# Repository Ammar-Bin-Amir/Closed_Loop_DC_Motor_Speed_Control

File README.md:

# Closed Loop DC Motor Speed Control

A speed control system's goal is to keep the motor's speed constant under a variety of circumstances. The DC motor is a nonlinear device in practice and speed variations are caused by disturbances, changes in load demand, etc. In this projet, the PID controller algorithm, a common controller in industries, has been implemented which overcome the disturbances occurring in the system and establishes the motor speed to the desired value without any human assistance.

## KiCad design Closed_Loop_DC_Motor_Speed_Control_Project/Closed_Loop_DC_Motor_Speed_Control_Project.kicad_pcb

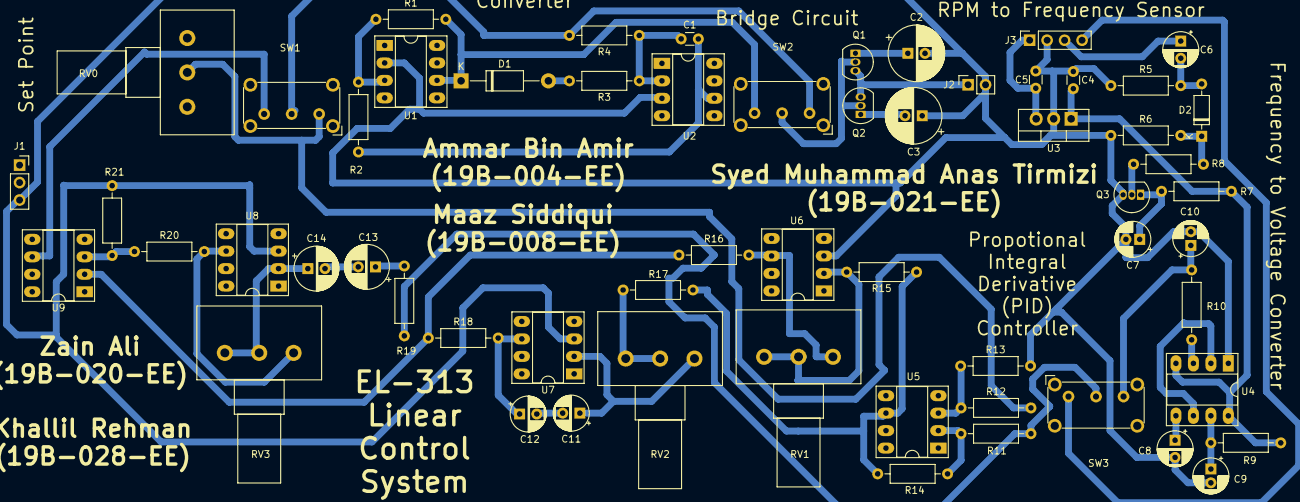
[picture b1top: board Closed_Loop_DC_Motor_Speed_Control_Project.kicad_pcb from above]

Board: 2 copper layers, 59 parts (0 on the bottom side), 41 nets.

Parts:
C1: 0.01μF; C_Disc_D3.0mm_W1.6mm_P2.50mm
C2, C3: 470μF,16VDC; CP_Radial_D8.0mm_P2.50mm
C4: 0.22μF; C_Disc_D3.0mm_W1.6mm_P2.50mm
C5: 0.1μF; C_Disc_D3.0mm_W1.6mm_P2.50mm
C6: 47μF; CP_Radial_D5.0mm_P2.50mm
C7, C9, C10: 0.022μF; CP_Radial_D5.0mm_P2.00mm
C8: 0.1μF; CP_Radial_D5.0mm_P2.50mm
C11, C12: 470μF; CP_Radial_D5.0mm_P2.50mm
C13, C14: 100μF; CP_Radial_D6.3mm_P2.50mm
D1: 1N4001; D_DO-41_SOD81_P12.70mm_Horizontal
D2: 1N4149; D_DO-35_SOD27_P7.62mm_Horizontal
J1: Power Supply; PinSocket_1x03_P2.54mm_Vertical
J2: DC Motor; PinSocket_1x02_P2.54mm_Vertical
J3: IR Sensor; PinSocket_1x04_P2.54mm_Vertical
Q1: BC547; TO-92_Inline
Q2: BC557; TO-92_Inline
Q3: BC337; TO-92_Inline
R1, R2, R3, R4, R11, R12, R13, R14, R15, R16, R18, R20, R21: 10kΩ; R_Axial_DIN0207_L6.3mm_D2.5mm_P10.16mm_Horizontal
R5, R17: 1kΩ; R_Axial_DIN0207_L6.3mm_D2.5mm_P10.16mm_Horizontal
R6, R7, R9: 47kΩ; R_Axial_DIN0207_L6.3mm_D2.5mm_P10.16mm_Horizontal
R8: 15kΩ; R_Axial_DIN0207_L6.3mm_D2.5mm_P10.16mm_Horizontal
R10: 4.7kΩ; R_Axial_DIN0207_L6.3mm_D2.5mm_P10.16mm_Horizontal
R19: 200Ω; R_Axial_DIN0207_L6.3mm_D2.5mm_P10.16mm_Horizontal
RV0, RV1, RV2, RV3: 100kΩ; Potentiometer_Alps_RK163_Single_Horizontal
SW1, SW2, SW3: SW_DPDT_x2; SW_E-Switch_EG1224_SPDT_Angled
U1, U2, U5, U6, U7, U8, U9: LM741; DIP-8_W7.62mm_Socket_LongPads
U3: LM7805_TO220; TO-220-3_Vertical
U4: LM555xM; DIP-8_W7.62mm_Socket_LongPads

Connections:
+12V: C2.1, C4.1, J1.1, Q1.1, R8.2, R9.2, RV0.1, U1.7, U2.7, U3.1, U4.4, U4.8, U5.7, U6.7, U7.7, U8.7, U9.7
-12V: C3.2, J1.2, Q2.1, RV0.3, U1.4, U2.4, U5.4, U6.4, U7.4, U8.4, U9.4
A_out: J3.4, SW3.1
BridgeIn: Q1.2, Q2.2, SW2.2
BridgeOut: J2.1, Q1.3, Q2.3
D_out: C6.1, J3.3
Derivative: R20.2, RV3.3, U8.6
F_to_V: C10.1, R10.1, SW3.3
GND: C2.2, C3.1, C4.2, C5.2, C7.2, C8.2, C9.2, C10.2, J1.3, J2.2, J3.2, Q3.3, R5.1, R6.1, R13.2, R21.2, U1.2, U2.3, U3.2, U4.1, U6.3, U7.3, U8.3
Input: R4.2, SW1.2, SW2.1
Integral: C12.1, R18.2, U7.6
unnamed: C1.1, R3.1, R4.1, U2.2
unnamed: C1.2, R2.1, U2.6
unnamed: C5.1, J3.1, U3.3
unnamed: C6.2, D2.2, R5.2
unnamed: C7.1, Q3.1, R8.1
unnamed: C8.1, U4.5
unnamed: C9.1, R9.1, U4.7
unnamed: C11.1, RV2.3, U7.2
unnamed: C11.2, C12.2
unnamed: C13.1, R19.1
unnamed: C13.2, C14.2
unnamed: C14.1, RV3.1, RV3.2, U8.2
unnamed: D1.2, R3.2
unnamed: D2.1, R6.2, R7.1
unnamed: Q3.2, R7.2
unnamed: R1.1, R2.2, U1.3
unnamed: R10.2, U4.3
unnamed: R11.1, R14.2, U5.2
unnamed: R12.1, R13.1, U5.3
unnamed: R14.1, R15.1, R17.1, U5.6
unnamed: R15.2, RV1.1, RV1.2, U6.2
unnamed: R16.1, R18.1, U9.2
unnamed: R17.2, RV2.1, RV2.2
unnamed: R20.1, R21.1, U9.3
unnamed: U4.2, U4.6
Output: R11.2, R19.2, SW3.2
PID: SW1.3, U9.6
Propotional: R16.2, RV1.3, U6.6
SetPoint: R12.2, RV0.2, SW1.1
V_to_F: D1.1, R1.2, SW2.3, U1.6
